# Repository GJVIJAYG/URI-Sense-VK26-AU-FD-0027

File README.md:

# URI-Sense-VK26-AU-FD-0027
Stage 2 Technical Audit &amp; Hardware Documentation

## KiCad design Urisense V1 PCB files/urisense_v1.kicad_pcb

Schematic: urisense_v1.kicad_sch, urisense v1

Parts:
C1: 0.1uF; C0805
C2: 1uF; C0805
C3, C4, C5: 100nF; C0805
C6: 10uF; C0805
C7: 22uF; C0805
CN1: B3B-PH-K-S; CONN-TH_B3B-PH-K-S; MPN B3B-PH-K-S(LF)(SN); LCSC C131339
CN2: SM05B-SRSS-TB; CONN-SMD_SM05B-SRSS-TB-LF-SN; MPN SM05B-SRSS-TB(LF)(SN); LCSC C136657
D1: USBLC6-2SC6; SOT-23-6_L2.9-W1.6-P0.95-LS2.8-BL; MPN USBLC6-2SC6; LCSC C7519
D2: MBR0520LT1G; SOD-123_L2.8-W1.8-LS3.7-RD; MPN MBR0520LT1G; LCSC C23848
D3: SS34_C8678; SMA_L4.3-W2.6-LS5.2-RD; MPN SS34; LCSC C8678
D4: SMBJ5.0A_C83333; SMB_L4.6-W3.6-LS5.3-RD; MPN SMBJ5.0A; LCSC C83333
L1: 22µH; IND-SMD_L4.0-W4.0_LQH44PN2R2MP0L; MPN SMNR4020-22UH; LCSC C135264
L2: GZ2012D101TF; L0805; MPN GZ2012D101TF; LCSC C1015
LED1: WS2812B-V5/W; LED-SMD_4P-L5.0-W5.0-TL-1; MPN WS2812B-V5/W; LCSC C2874885
LED2: KT-0603R; LED-SMD_L1.6-W0.8-R-RD; MPN KT-0603R; LCSC C2286
LED3: KT-0802; LED-SMD_L2.0-W0.5-R-RD; MPN KT-0802 翠绿; LCSC C185659
Q1: AO3401A; SOT-23_L2.9-W1.3-P1.90-LS2.4-BR; MPN AO3401A; LCSC C15127
Q2: 2N7002; SOT-23-3_L2.9-W1.3-P1.90-LS2.4-BR; MPN 2N7002; LCSC C8545
R1, R2: 5.1k; R0805
R3: 1.2k; R0805
R4, R5, R11, R13: 1k; R0805
R6: 100k; R0805
R7, R9, R10, R12: 10k; R0805
R8: 2.2k; R0805
R14: 10; R0805
R15, R16: 4.7k; R0805
SW1, SW2: HX-6X6X7.3-TP FT SQUARE BUTTON; SW-SMD_4P-L6.0-W6.0-P4.50-LS9.0-H7.3; MPN HX-6x6x7.3-TP FT square button; LCSC C49234152
U1: TP4056_C382139; ESOP-8_L4.9-W3.9-P1.27-LS6.0-BL-EP; MPN TP4056; LCSC C382139
U2: AP2112K-3.3TRG1; SOT-25-5_L2.9-W1.6-P0.95-LS2.8-BL; MPN AP2112K-3.3TRG1; LCSC C51118
U3: MT3608; SOT-23-6_L2.9-W1.6-P0.95-LS2.8-BL; MPN MT3608; LCSC C84817
U4: ESP32-S3-WROOM-1-N4; WIFIM-SMD_ESP32-S3-WROOM-1-N8; MPN ESP32-S3-WROOM-1-N4; LCSC C2913197
U5: DRV8837DSGR; WSON-8_L2.0-W2.0-P0.50-TL-EP; MPN DRV8837DSGR; LCSC C39159
U6, U7: S2B-XH-A-; CONN-TH_S2B-XH-A-LF-SN; MPN S2B-XH-A(LF)(SN); LCSC C157931
USB1: USB4120-03-C; TYPE-C-SMD_USB4120-03-C; MPN USB4120-03-C; LCSC C3445864

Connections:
BOOT_SW: R10.1, SW2.1 (A), SW2.2 (B), U4.27 (IO0)
I2C_SCL: CN2.4, R16.2, U4.5 (IO5)
I2C_SDA: CN2.3, R15.2, U4.4 (IO4)
LED_CATHODE: CN2.6, Q2.3 (D)
LED_EN: C5.2, Q2.1 (G), R13.1, U4.7 (IO7)
L_VOUT: D3.2 (A), L1.2
MOTOR_FWD: U4.11 (IO18), U5.6 (IN1)
N_01AE718B: C6.1, D2.1 (C), Q1.3 (D), U2.1 (VIN), U2.3 (EN), U3.4 (EN), U3.5 (IN)
N_02AE731E: C1.2, C2.1, C4.1, C5.1, C6.2, C7.2, CN1.2, CN2.2, CN2.7, D1.2, D4.2, LED1.3 (VSS), R1.1, R2.2, R3.1, R8.1, R14.2, SW1.3 (C), SW1.4 (D), SW2.3 (C), SW2.4 (D), U1.3 (GND), U1.8 (CE), U2.2 (GND), U3.2 (GND), U4.1 (GND), U4.40 (GND), U4.41 (GND), U5.4 (GND), U7.2, USB1.0, USB1.A1 (GND), USB1.A12 (GND), USB1.B1 (GND), USB1.B12 (GND)
N_3V3_OPT: CN2.1, L2.2
N_5V_BOOST: D3.1 (K), D4.1, R7.2, U5.1 (VM)
unnamed: LED2.1 (A), R4.1
unnamed: LED2.2 (K), U1.7 (~CHRG)
unnamed: LED3.1 (A), R5.1
unnamed: LED3.2 (B), U1.6 (~STDBY)
unnamed: Q2.2 (S), R14.1
unnamed: R3.2, U1.2 (PROG)
unnamed: L1.1, U3.1 (SW)
unnamed: R13.2, U4.12 (IO8)
unnamed: R11.1, U4.23 (IO21)
unnamed: R1.2, USB1.A5 (CC1)
unnamed: R2.1, USB1.B5 (CC2)
OUT1: C3.2, U5.2 (OUT1), U6.1
OUT2: C3.1, U5.3 (OUT2), U6.2
RESET_SW: C2.2, R9.2, SW1.1 (A), SW1.2 (B), U4.3 (EN)
RGB_LED: LED1.4 (DIN), U4.25 (IO48)
SENSOR_INT: CN2.5, U4.6 (IO6)
SERIES_R7_N_1_U3_FB: R7.1, R8.2, U3.3 (FB)
SERIES_R11_N_2_U7_N_1: C4.2, R11.2, R12.2, U7.1
U2_VOUT: C1.1, C7.1, L2.1, LED1.1 (VDD), R9.1, R10.2, R12.1, R15.1, R16.1, U2.5 (VOUT), U4.2 (3V3), U5.7 (nSPLEEP), U5.8 (VCC)
USB_DN: D1.3, D1.4, U4.13 (IO19), U5.5 (IN2), USB1.A7 (Dn1), USB1.B7 (Dn2)
USB_DP: D1.1, D1.6, U4.14 (IO20), USB1.A6 (Dp1), USB1.B6 (Dp2)
VBAT: CN1.1, Q1.2 (S), U1.5 (BAT)
VBUS: D2.2 (A), Q1.1 (G), R4.2, R5.2, R6.1, R6.2, U1.4 (VCC), USB1.A4 (VBUS), USB1.A9 (VBUS), USB1.B4 (VBUS), USB1.B9 (VBUS)

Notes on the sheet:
ESP32-S3 MCU & Control Logic
IO & Peripheral Connectors
PROTOFLOW_REGION:eyJpZCI6ImZpbmFsLXNlY3Rpb24tNmQ0MDIzZjQ3OTBlYWNjZCIsIm5hbWUiOiJFU1AzMi1TMyBNQ1UgJiBDb250cm9sIExvZ2ljIiwieDEiOjM1MTcuODk5OTk5OTk5OTk5NiwieTEiOjcyMy45LCJ4MiI6NDkyNy41OTk5OTk5OTk5OTksInkyIjoxOTgxLjE5OTk5OTk5OTk5OTgsImNvbG9yIjo0MjgyNDI3NTA0LCJkZXNjcmlwdGlvbiI6bnVsbCwiY29tcG9uZW50SWRzIj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
PROTOFLOW_REGION:eyJpZCI6ImZpbmFsLXNlY3Rpb24tZDZiYjBhYzNkYjAyZjJiZCIsIm5hbWUiOiJQb3dlciBNYW5hZ2VtZW50IiwieDEiOjEwMTYuMCwieTEiOjcyMy45LCJ4MiI6MzQxNi4yOTk5OTk5OTk5OTk3LCJ5MiI6MTk4MS4xOTk5OTk5OTk5OTk4LCJjb2xvciI6NDI4MzI2OTMyNSwiZGVzY3JpcHRpb24iOm51bGwsImNvbXBvbmVudElkcyI6WyJhNWYwMWRjZS0xYzE5LTQ3NjAtYj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
Power Management
PROTOFLOW_REGION:eyJpZCI6ImZpbmFsLXNlY3Rpb24tNGUxMmEwN2MzYWQ0N2EyYiIsIm5hbWUiOiJJTyAmIFBlcmlwaGVyYWwgQ29ubmVjdG9ycyIsIngxIjoxMDE2LjAsInkxIjoyMDgyLjc5OTk5OTk5OTk5OTcsIngyIjozNDE2LjI5OTk5OTk5OTk5OTcsInkyIjozMjc2LjYsImNvbG9yIjo0Mjg5MzYwMDc3LCJkZXNjcmlwdGlvbiI6bnVsbCwiY29tcG9uZW50SWRzIjpbIjZmNzc0YzVjLT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

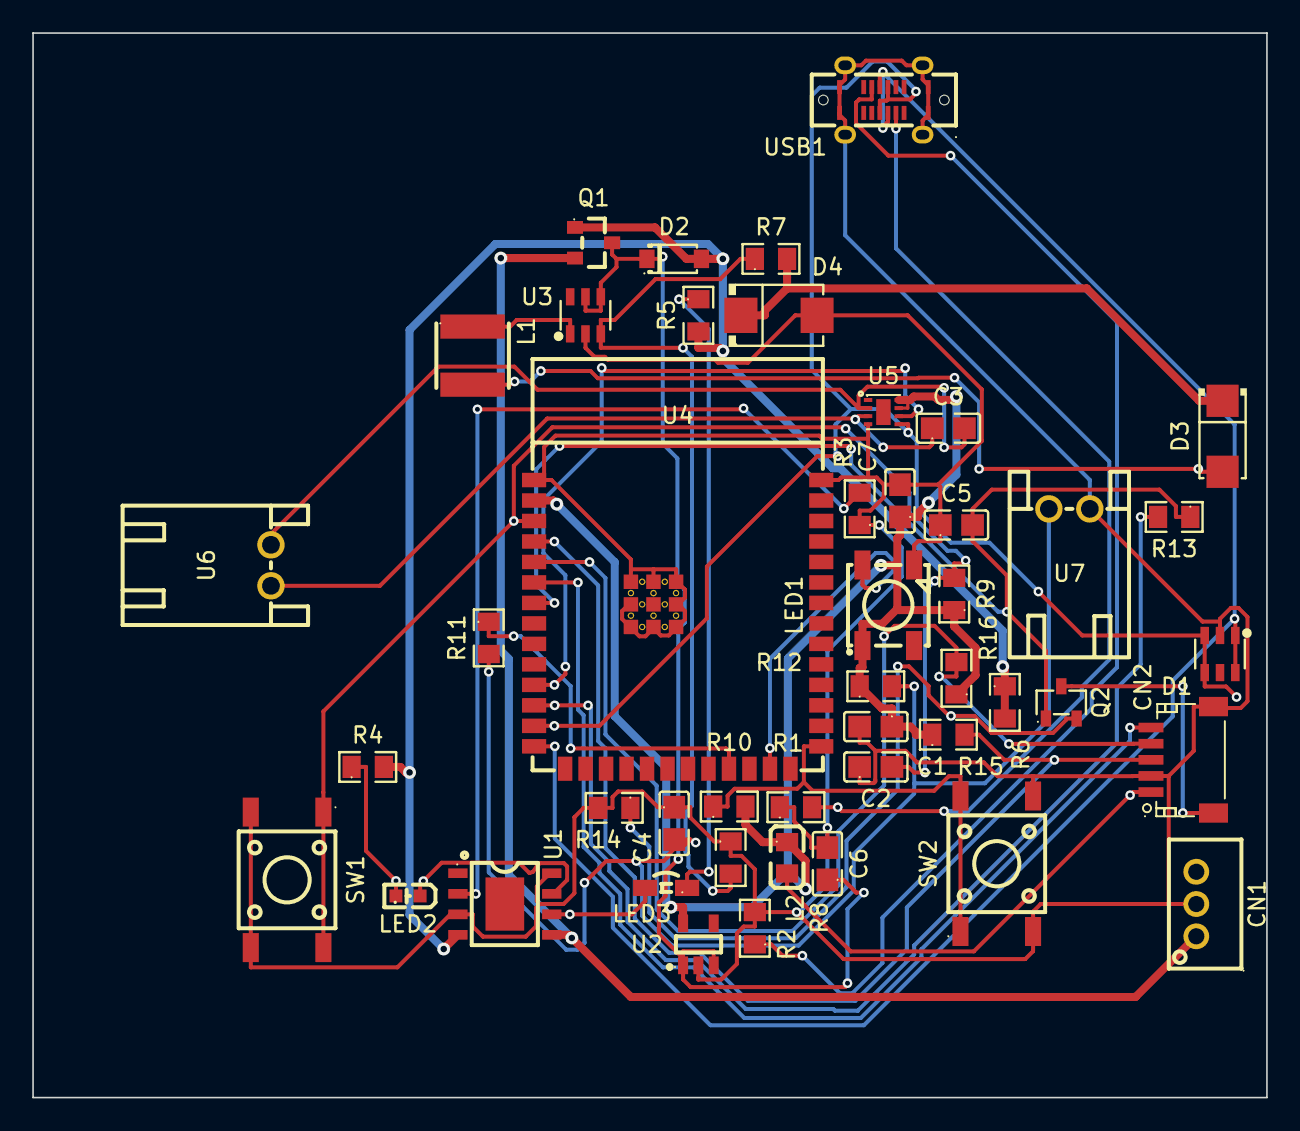
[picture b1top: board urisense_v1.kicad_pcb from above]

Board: 2 copper layers, 76.5 x 66.0 mm, 46 parts (0 on the bottom side), 34 nets.
